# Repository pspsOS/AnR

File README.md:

# AnR: PSPS Avionics and Recovery GitHub
This document was last edited by Jeffrey Kaji on *4 Feb 2021*. <br/>
View our license [here](LICENSE)

## MITCH_2021
**Multi-Instrument Telemetry Computer Hardware** for PSPS 2021 Rocket<br> 
Important Macros: <br>
``getBit(A, X)`` : gets the *"Xth"* bit of *"A"*.<br>
``setBit(A, X, V)`` : sets the *"Xth"* bit of *"A"* to *"V"*.<br><br>

#### Quick Links
* [Documentation Folder **Docs/**](../Docs/README.md)
* [**Recovery-Avionics Jira**](https://psps-recovery-avionics.atlassian.net/jira/software/projects/AV/boards/2)
* [**SRAD Software Confluence Page**](https://psps-recovery-avionics.atlassian.net/wiki/spaces/PSPS/pages/31457281/SRAD+Software)
* [**Task Flowcharts Google Drive Folder**](https://drive.google.com/drive/u/0/folders/1KGmiUlNgTaysgdSle6QIzn_O4cT77nek)
* [**Hardware Datasheets Google Drive Folder**](https://drive.google.com/drive/u/0/folders/14jC0XhoOVIF4Ko5ylgHbCWUhaxgak8n0)

---
**Creating a *README.md*?** <br />
 Try using this free online editor that makes it super easy: 
<https://jbt.github.io/markdown-editor/>

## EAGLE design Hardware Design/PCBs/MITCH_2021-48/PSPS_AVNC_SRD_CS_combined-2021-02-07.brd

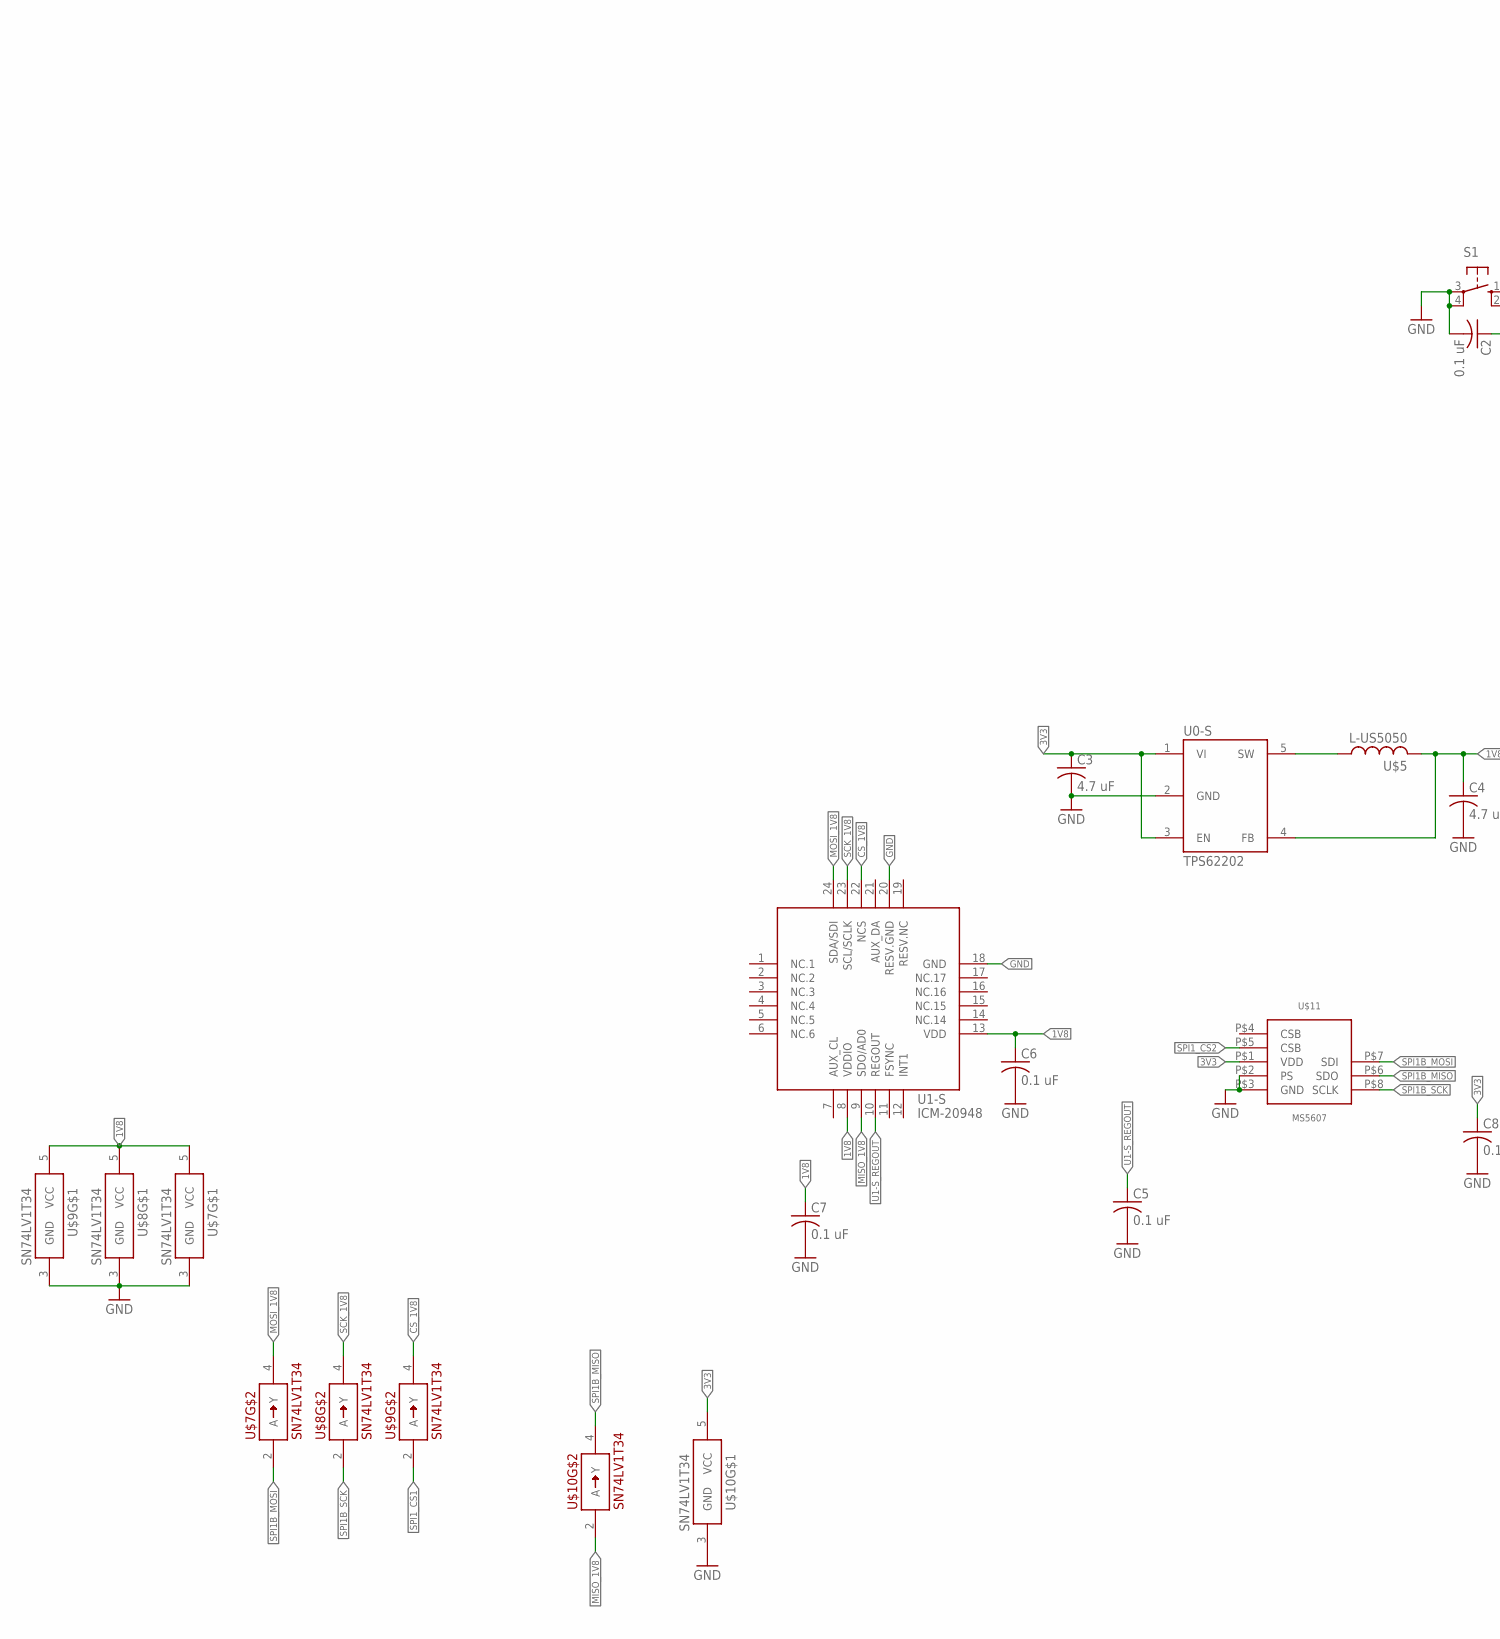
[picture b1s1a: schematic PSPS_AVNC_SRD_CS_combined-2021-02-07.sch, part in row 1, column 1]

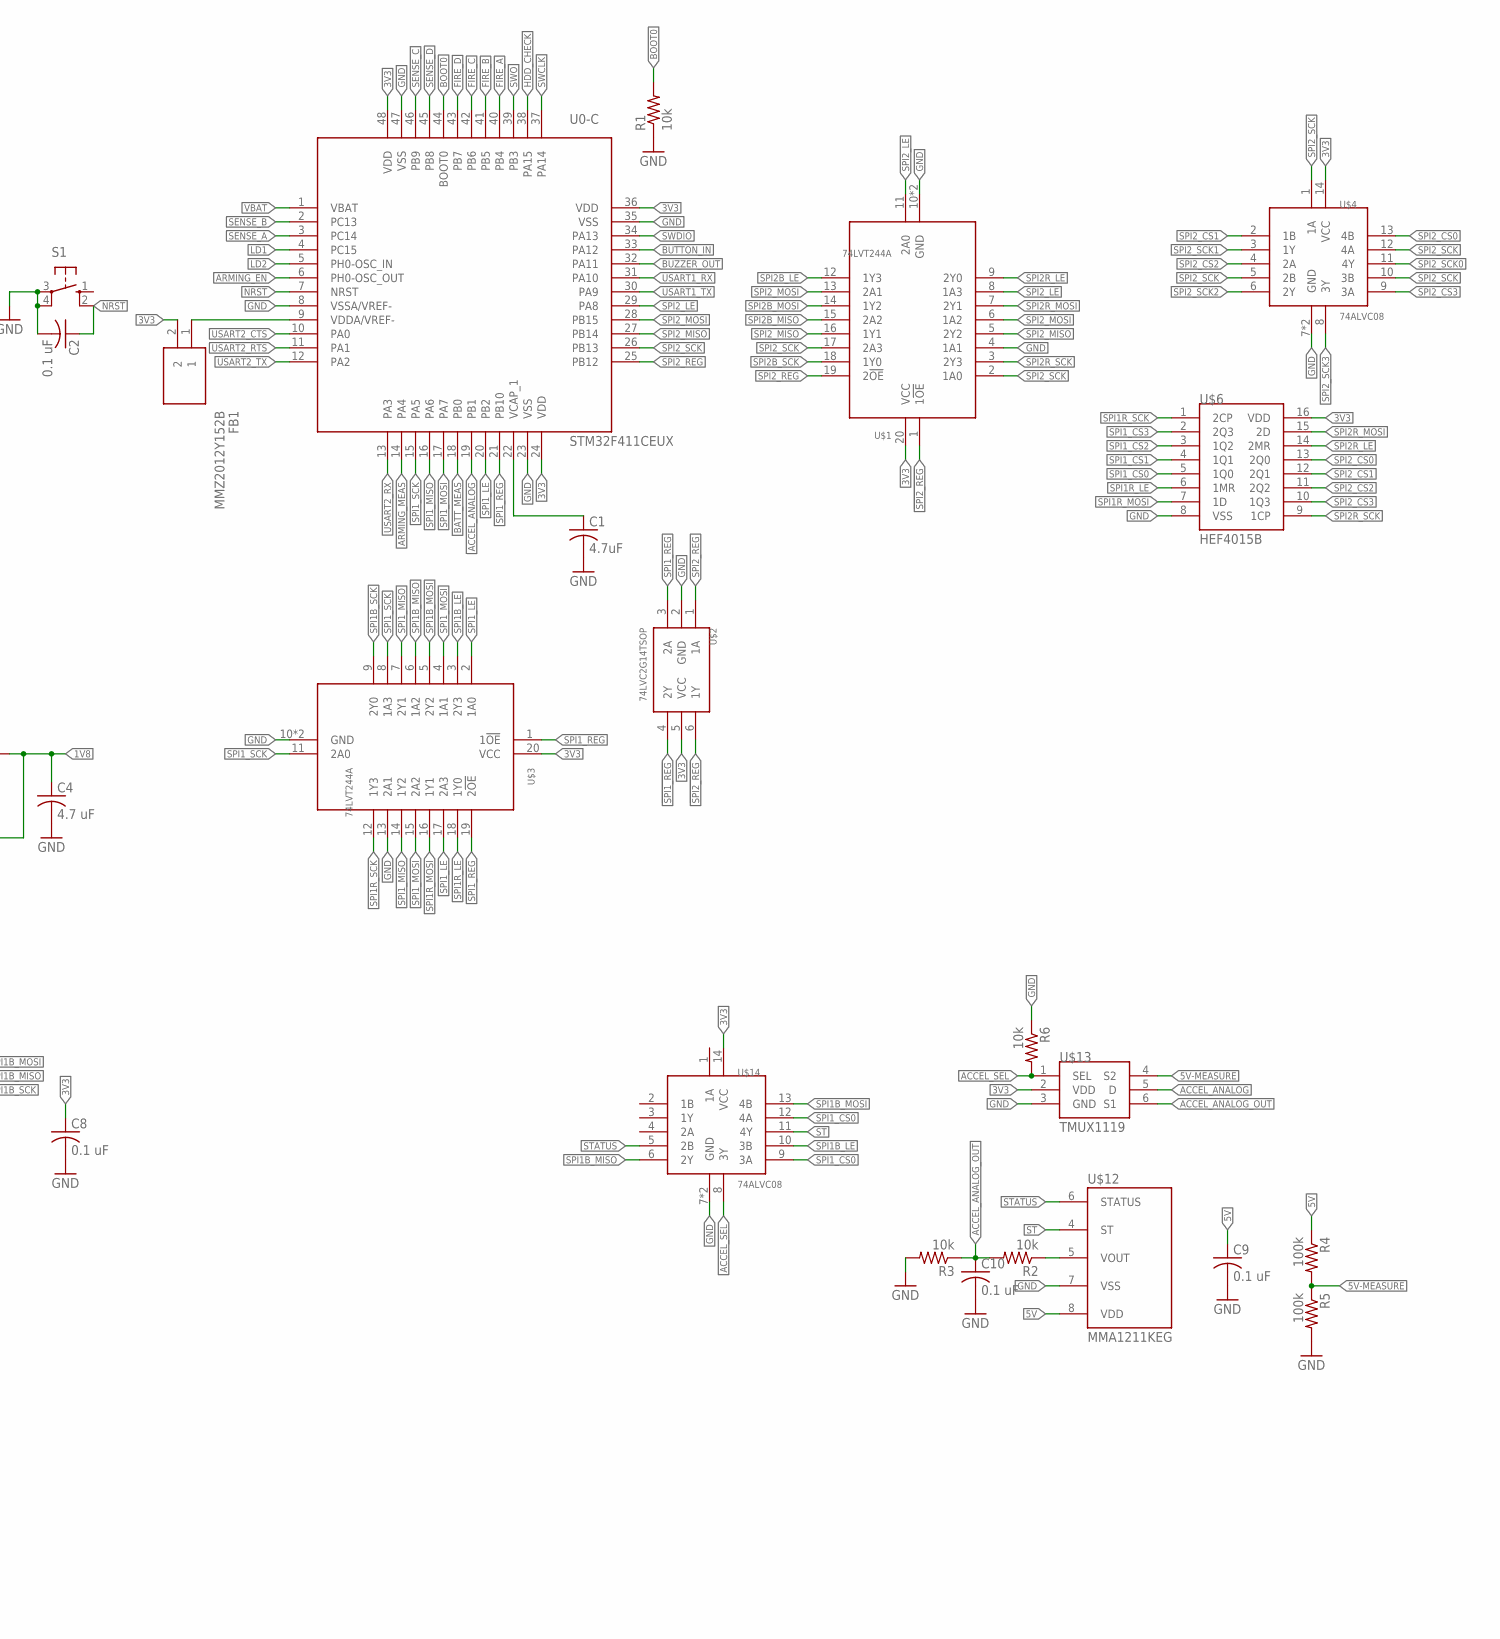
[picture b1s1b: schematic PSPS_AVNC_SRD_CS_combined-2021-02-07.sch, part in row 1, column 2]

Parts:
C1: 4.7uF; C0805
C2, C5, C6, C7, C8, C9, C10: 0.1 uF; C0805
C3, C4: 4.7 uF; C0805
FB1: MMZ2012Y152B; BEADC2012X105N
R1, R2, R3, R6: 10k; M0805
R4, R5: 100k; M0805
S1: 10-XX; B3F-10XX
U0-C: STM32F411CEUX; QFN50P700X700X50-49T560N
U0-S: TPS62202; SOT95P280X145-5
U1-S: ICM-20948; QFN40P300X300X105-25T159X175
U$1, U$3: 74LVT244A; QFN50P450X250X100-21T300X100N
U$2: 74LVC2G14TSOP; SOP95P280X110-6N
U$4, U$14: 74ALVC08; QFN50P300X250X100-15T150X100N
U$5: L-US5050; INDDFN1250X1250X600-2N
U$6: HEF4015B; SOIC127P600X265-16N
U$7, U$8, U$9, U$10: SN74LV1T34; SOT65P210X110-5
U$11: MS5607
U$12: MMA1211KEG; SOIC127P1041X355-16N
U$13: TMUX1119; SOP95P280X145-6N

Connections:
1V8: C4.1, C6.1, C7.1, U0-S.4 (FB), U1-S.8 (VDDIO), U1-S.13 (VDD), U$5.2, U$7.5 (VCC), U$8.5 (VCC), U$9.5 (VCC)
3V3: C3.1, C8.1, FB1.2, U0-C.24 (VDD), U0-C.36 (VDD), U0-C.48 (VDD), U0-S.1 (VI), U0-S.3 (EN), U$1.20 (VCC), U$2.5 (VCC), U$3.20 (VCC), U$4.14 (VCC), U$6.16 (VDD), U$10.5 (VCC), U$11.P$1 (VDD), U$13.2 (VDD), U$14.14 (VCC)
5V: C9.1, R4.1, U$12.8 (VDD)
5V-MEASURE: R4.2, R5.1, U$13.4 (S2)
!SPI1_REG!: U$2.4 (2Y), U$3.19 (2!OE!)
!SPI2_REG!: U$1.1 (1!OE!), U$2.6 (1Y)
ACCEL_ANALOG: U0-C.19 (PB1), U$13.5 (D)
ACCEL_ANALOG_OUT: C10.1, R2.2, R3.1, U$13.6 (S1)
ACCEL_SEL: R6.2, U$13.1 (SEL), U$14.8 (3Y)
ARMING_EN: U0-C.6 (PH0-OSC_OUT)
ARMING_MEAS: U0-C.14 (PA4)
BATT_MEAS: U0-C.18 (PB0)
BOOT0: R1.2, U0-C.44 (BOOT0)
BUTTON_IN: U0-C.33 (PA12)
BUZZER_OUT: U0-C.32 (PA11)
CS_1V8: U1-S.22 (NCS), U$9.4 (Y)
FIRE_A: U0-C.40 (PB4)
FIRE_B: U0-C.41 (PB5)
FIRE_C: U0-C.42 (PB6)
FIRE_D: U0-C.43 (PB7)
GND: C1.2, C2.2, C3.2, C4.2, C5.2, C6.2, C7.2, C8.2, C9.2, C10.2, R1.1, R3.2, R5.2, R6.1, S1.3, S1.4 (P1), U0-C.8 (VSSA/VREF-), U0-C.23 (VSS), U0-C.35 (VSS), U0-C.47 (VSS), U0-S.2 (GND), U1-S.18 (GND), U1-S.20 (RESV.GND), U$1.4 (1A1), U$1.10 (GND), U$1.21 (GND), U$2.2 (GND), U$3.10 (GND), U$3.13 (2A1), U$3.21 (GND), U$4.7 (GND), U$4.15 (GND), U$6.8 (VSS), U$7.3 (GND), U$8.3 (GND), U$9.3 (GND), U$10.3 (GND), U$11.P$2 (PS), U$11.P$3 (GND), U$12.7 (VSS), U$13.3 (GND), U$14.7 (GND), U$14.15 (GND)
HDD_CHECK: U0-C.38 (PA15)
LD1: U0-C.4 (PC15)
LD2: U0-C.5 (PH0-OSC_IN)
MISO_1V8: U1-S.9 (SDO/AD0), U$10.2 (A)
MOSI_1V8: U1-S.24 (SDA/SDI), U$7.4 (Y)
NRST: C2.1, S1.2 (S1), U0-C.7 (NRST)
SCK_1V8: U1-S.23 (SCL/SCLK), U$8.4 (Y)
SENSE_A: U0-C.3 (PC14)
SENSE_B: U0-C.2 (PC13)
SENSE_C: U0-C.46 (PB9)
SENSE_D: U0-C.45 (PB8)
SPI1B_LE: U$3.3 (2Y3), U$14.10 (3B)
SPI1B_MISO: U$3.6 (1A2), U$10.4 (Y), U$11.P$6 (SDO), U$14.6 (2Y)
SPI1B_MOSI: U$3.5 (2Y2), U$7.2 (A), U$11.P$7 (SDI), U$14.13 (4B)
SPI1B_SCK: U$3.9 (2Y0), U$8.2 (A), U$11.P$8 (SCLK)
SPI1R_LE: U$3.18 (1Y0), U$6.6 (1MR)
SPI1R_MOSI: U$3.16 (1Y1), U$6.7 (1D)
SPI1R_SCK: U$3.12 (1Y3), U$6.1 (2CP)
SPI1_CS0: U$6.5 (1Q0), U$14.9 (3A), U$14.12 (4A)
SPI1_CS1: U$6.4 (1Q1), U$9.2 (A)
SPI1_CS2: U$6.3 (1Q2), U$11.P$5 (CSB)
SPI1_CS3: U$6.2 (2Q3)
SPI1_LE: U0-C.20 (PB2), U$3.2 (1A0), U$3.17 (2A3)
SPI1_MISO: U0-C.16 (PA6), U$3.7 (2Y1), U$3.14 (1Y2)
SPI1_MOSI: U0-C.17 (PA7), U$3.4 (1A1), U$3.15 (2A2)
SPI1_REG: U0-C.21 (PB10), U$2.3 (2A), U$3.1 (1!OE!)
SPI1_SCK: U0-C.15 (PA5), U$3.8 (1A3), U$3.11 (2A0)
SPI2B_LE: U$1.12 (1Y3)
SPI2B_MISO: U$1.15 (2A2)
SPI2B_MOSI: U$1.14 (1Y2)
SPI2B_SCK: U$1.18 (1Y0)
SPI2R_LE: U$1.9 (2Y0), U$6.14 (2MR)
SPI2R_MOSI: U$1.7 (2Y1), U$6.15 (2D)
SPI2R_SCK: U$1.3 (2Y3), U$6.9 (1CP)
SPI2_CS0: U$4.13 (4B), U$6.13 (2Q0)
SPI2_CS1: U$4.2 (1B), U$6.12 (2Q1)
SPI2_CS2: U$4.4 (2A), U$6.11 (2Q2)
SPI2_CS3: U$4.9 (3A), U$6.10 (1Q3)
SPI2_LE: U0-C.29 (PA8), U$1.8 (1A3), U$1.11 (2A0)
SPI2_MISO: U0-C.27 (PB14), U$1.5 (2Y2), U$1.16 (1Y1)
SPI2_MOSI: U0-C.28 (PB15), U$1.6 (1A2), U$1.13 (2A1)
SPI2_REG: U0-C.25 (PB12), U$1.19 (2!OE!), U$2.1 (1A)
SPI2_SCK: U0-C.26 (PB13), U$1.2 (1A0), U$1.17 (2A3), U$4.1 (1A), U$4.5 (2B), U$4.10 (3B), U$4.12 (4A)
SPI2_SCK0: U$4.11 (4Y)
SPI2_SCK1: U$4.3 (1Y)
SPI2_SCK2: U$4.6 (2Y)
SPI2_SCK3: U$4.8 (3Y)
ST: U$12.4 (ST), U$14.11 (4Y)
STATUS: U$12.6 (STATUS), U$14.5 (2B)
SWCLK: U0-C.37 (PA14)
SWDIO: U0-C.34 (PA13)
SWO: U0-C.39 (PB3)
U0-S_SW: U0-S.5 (SW), U$5.1
U0-S_VOUT: R2.1, U$12.5 (VOUT)
U1-S_REGOUT: C5.1, U1-S.10 (REGOUT)
USART1_RX: U0-C.31 (PA10)
USART1_TX: U0-C.30 (PA9)
USART2_CTS: U0-C.10 (PA0)
USART2_RTS: U0-C.11 (PA1)
USART2_RX: U0-C.13 (PA3)
USART2_TX: U0-C.12 (PA2)
VBAT: U0-C.1 (VBAT)
VCAP_1: C1.1, U0-C.22 (VCAP_1)
VDDA: FB1.1, U0-C.9 (VDDA/VREF-)

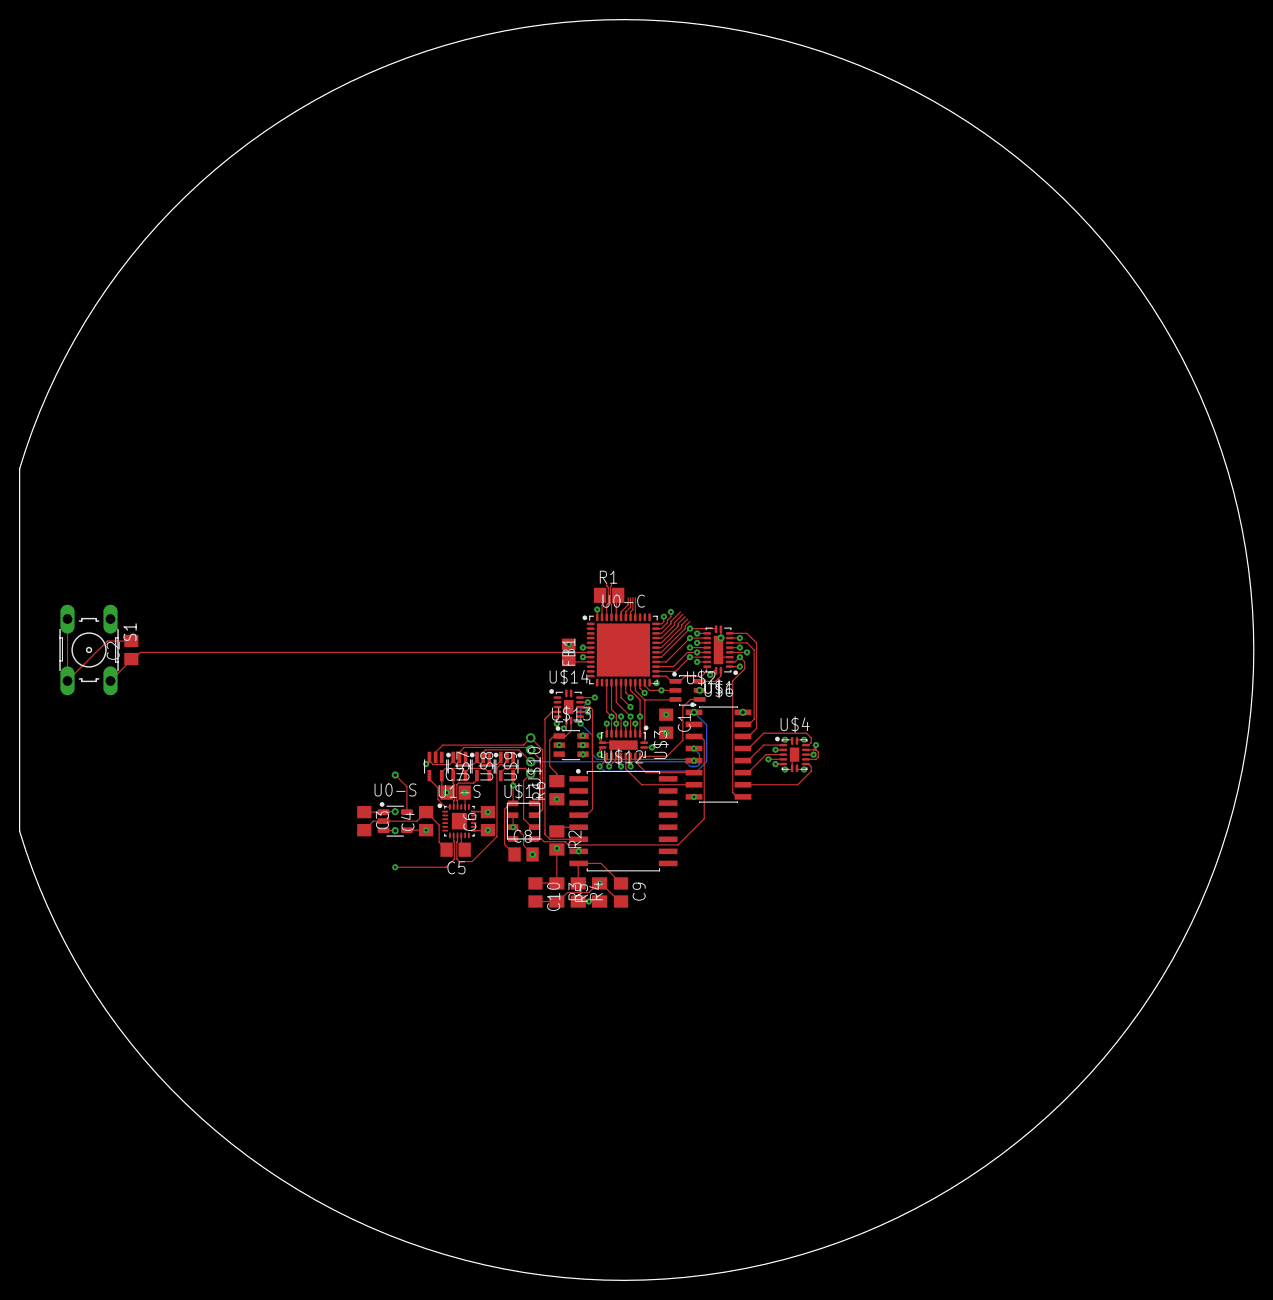
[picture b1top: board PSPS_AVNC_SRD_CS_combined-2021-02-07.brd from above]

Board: 4 copper layers, 129.8 x 132.6 mm, 35 parts (1 on the bottom side), 50 nets.

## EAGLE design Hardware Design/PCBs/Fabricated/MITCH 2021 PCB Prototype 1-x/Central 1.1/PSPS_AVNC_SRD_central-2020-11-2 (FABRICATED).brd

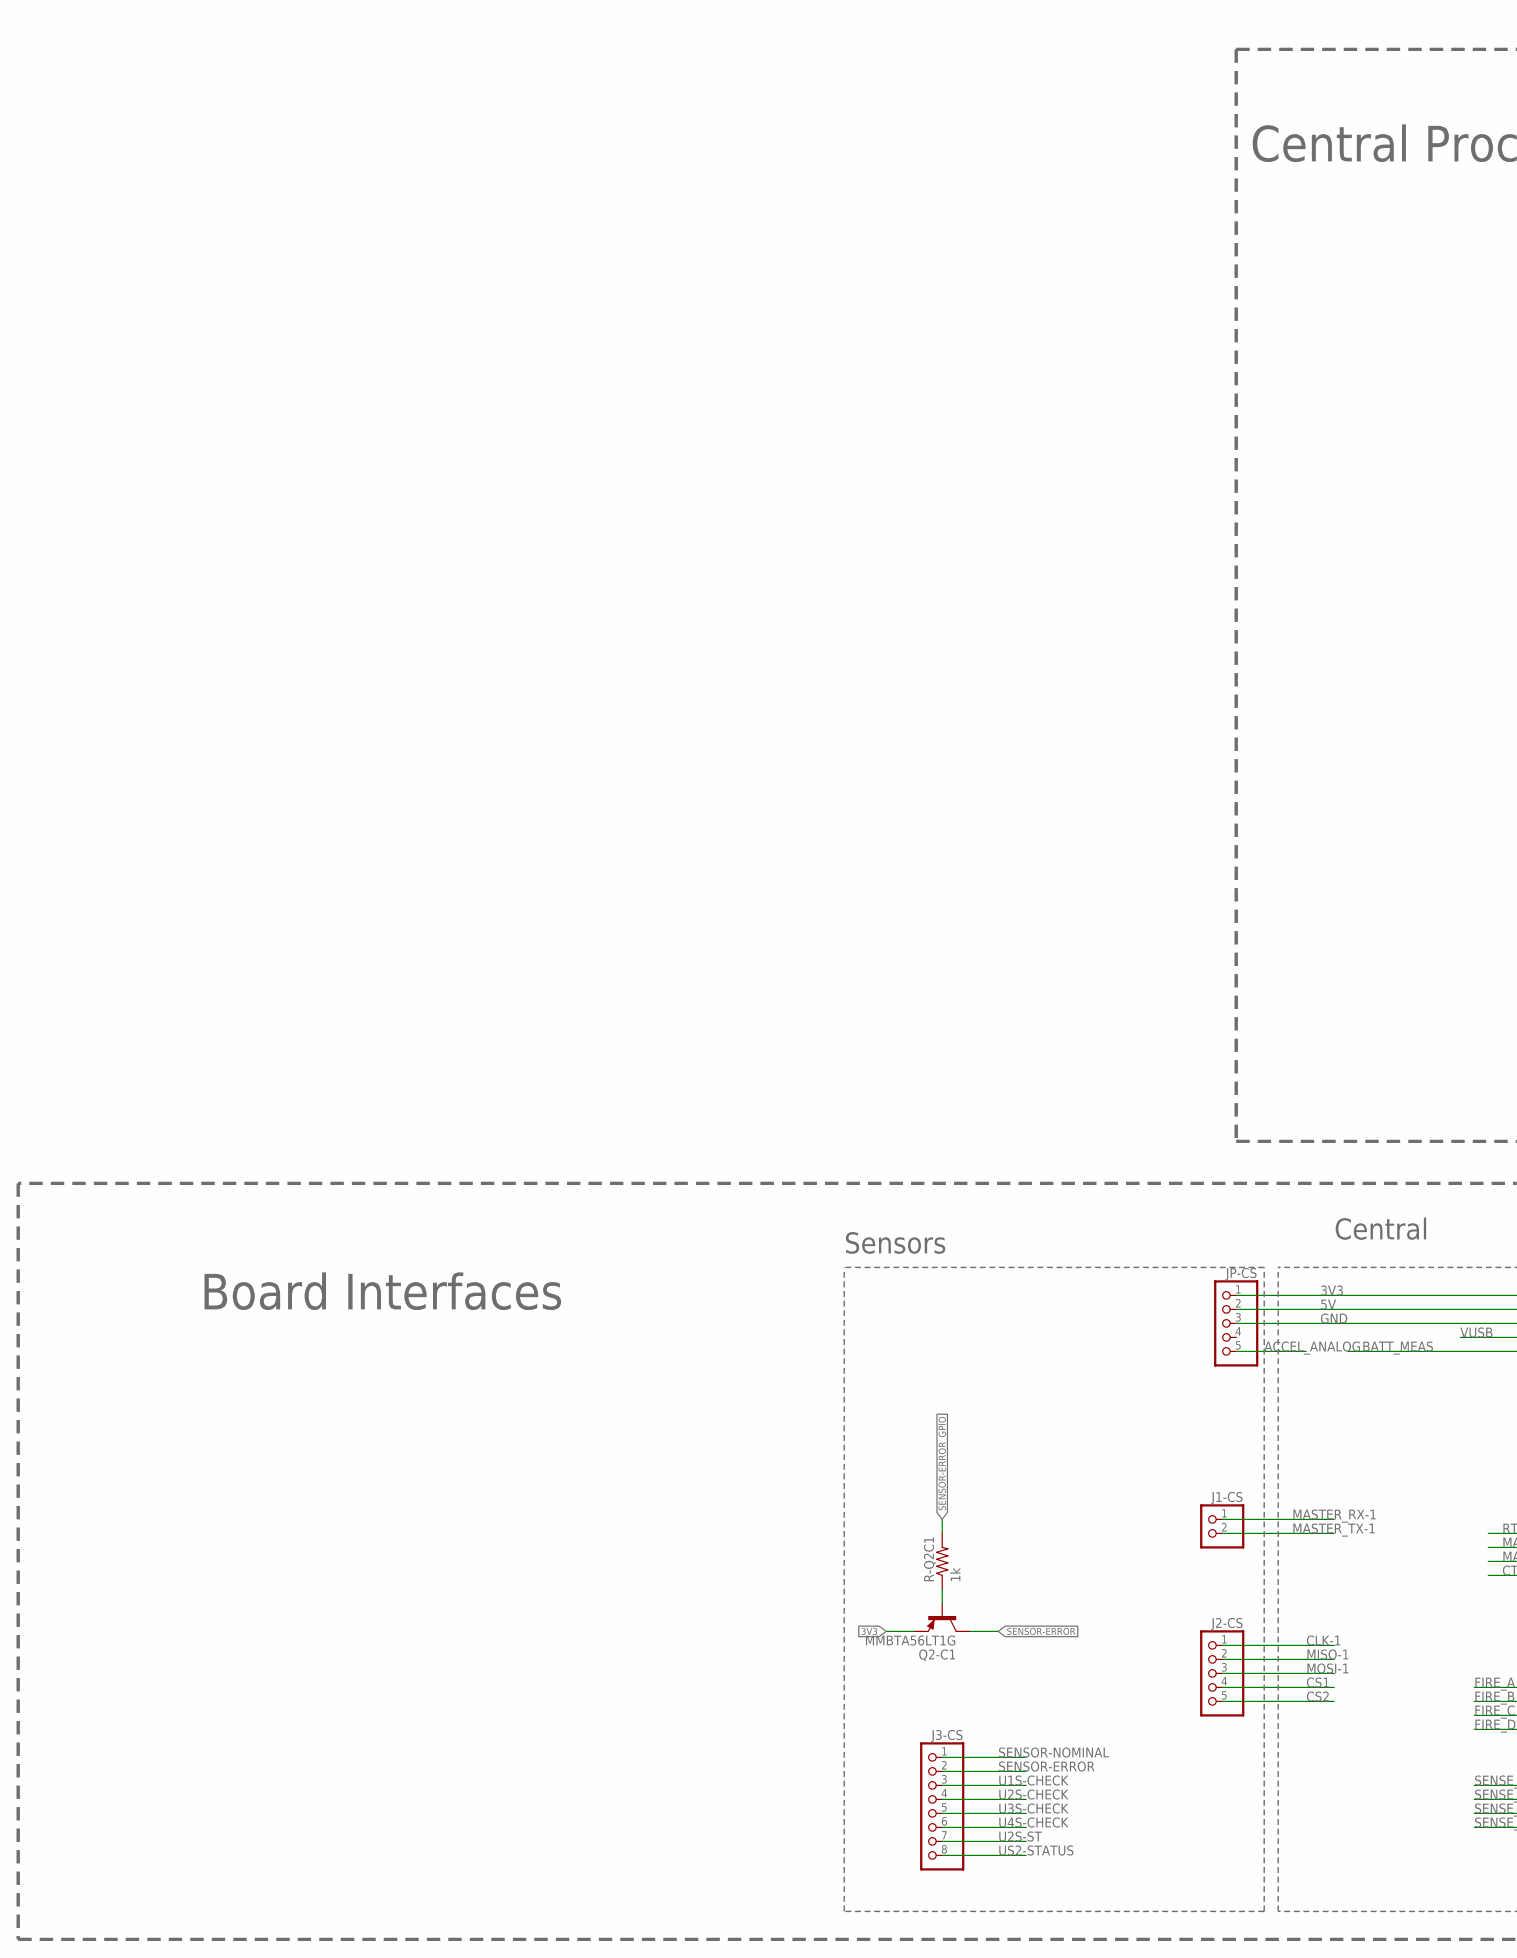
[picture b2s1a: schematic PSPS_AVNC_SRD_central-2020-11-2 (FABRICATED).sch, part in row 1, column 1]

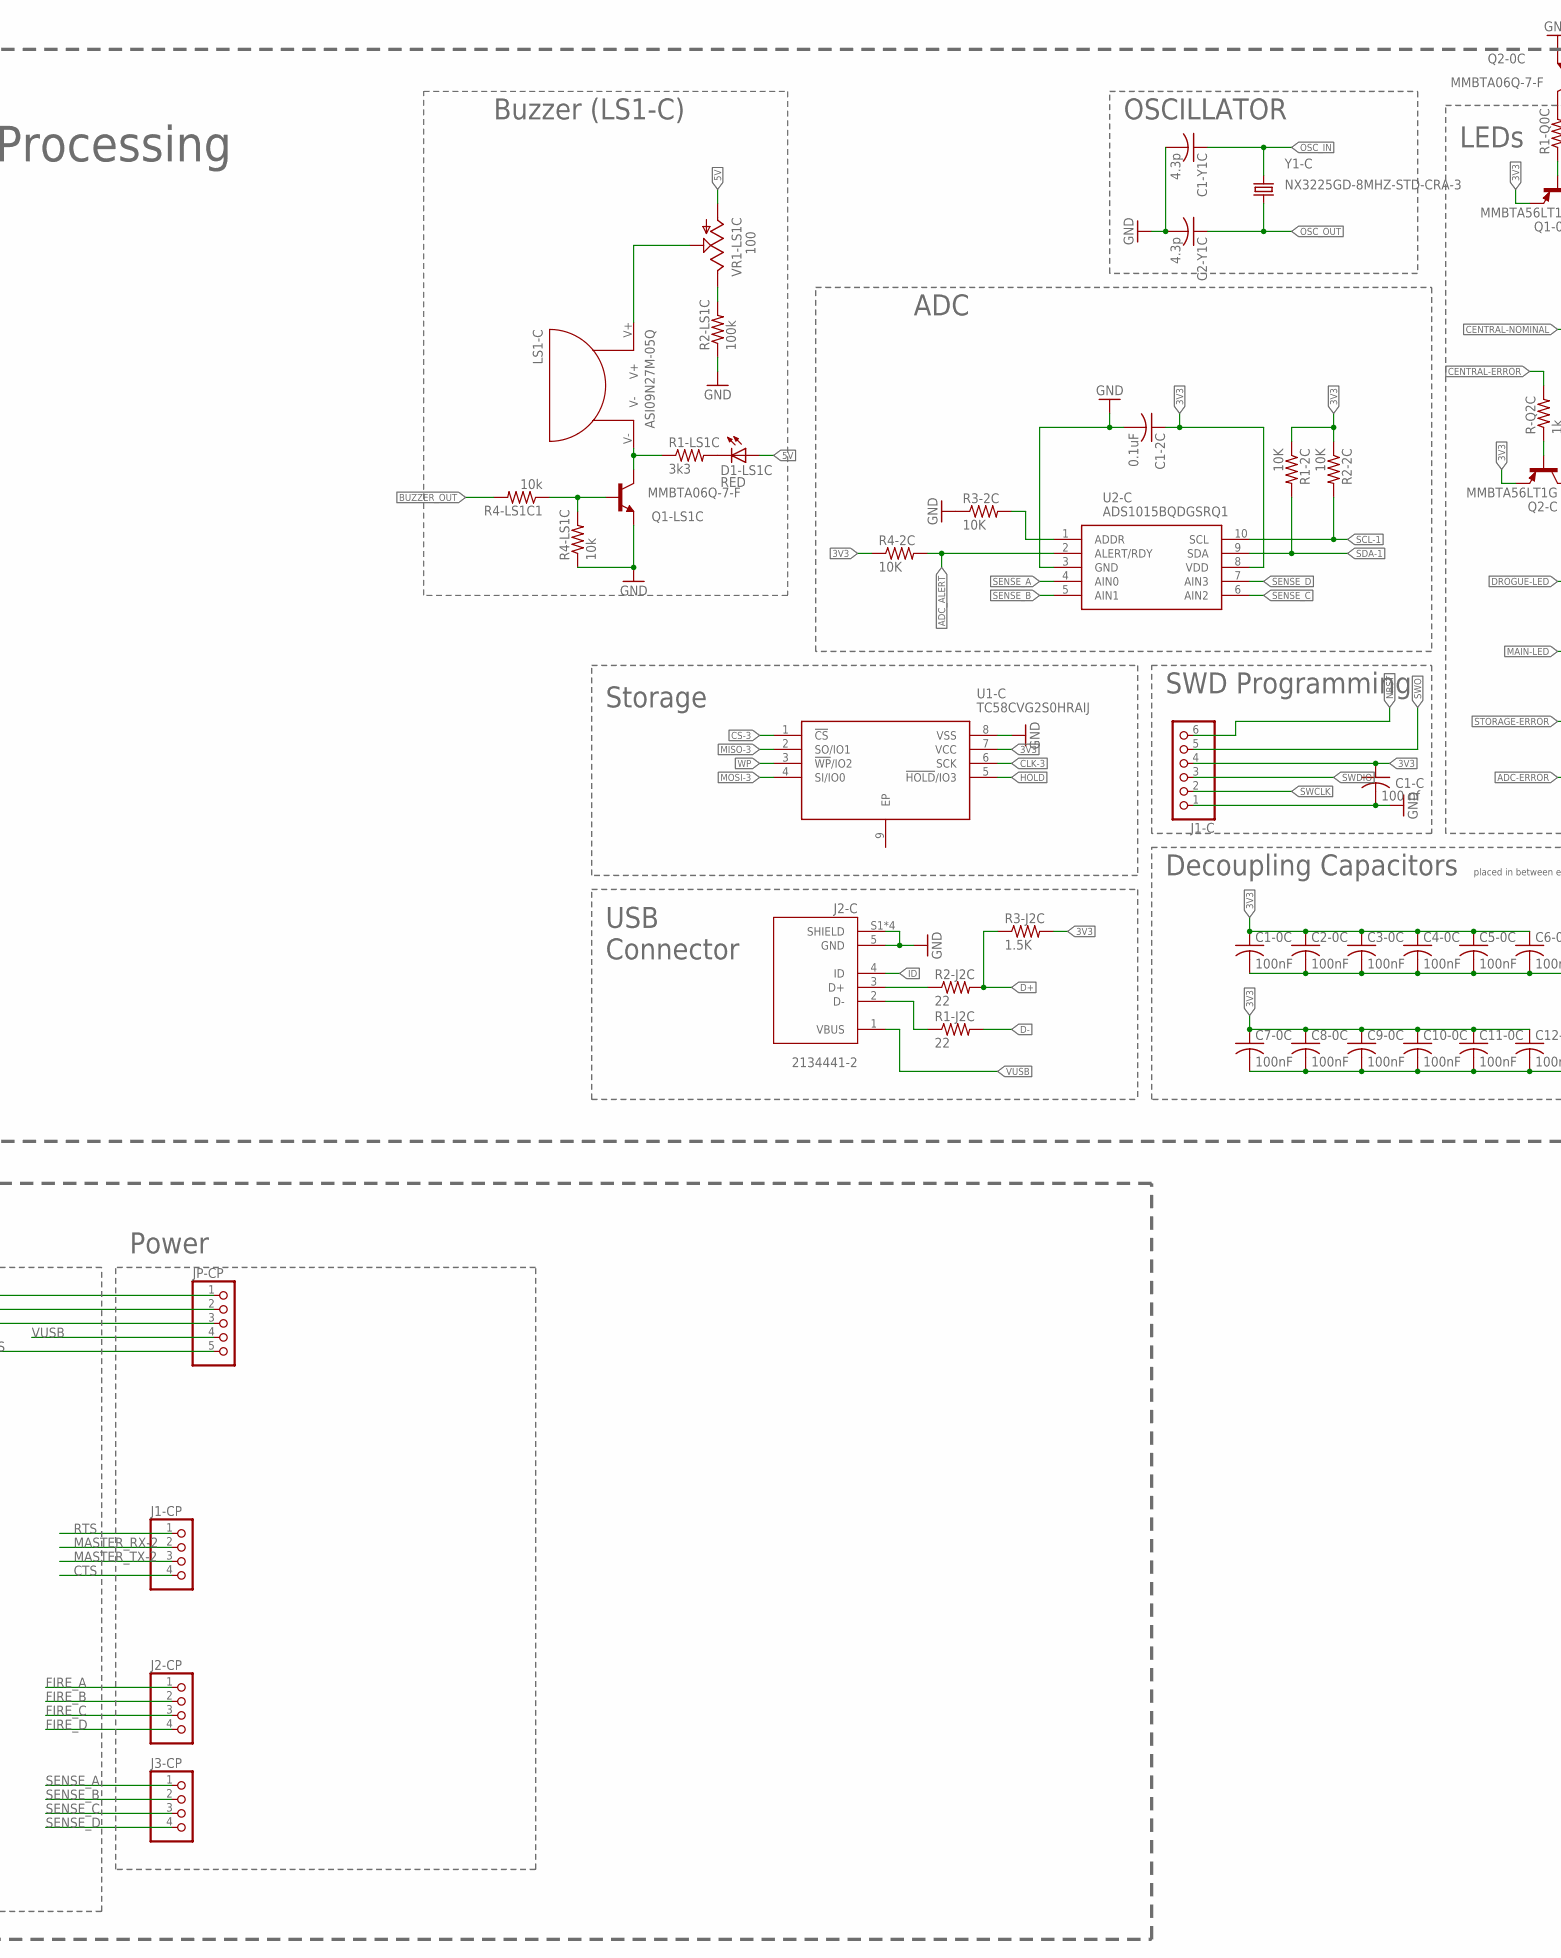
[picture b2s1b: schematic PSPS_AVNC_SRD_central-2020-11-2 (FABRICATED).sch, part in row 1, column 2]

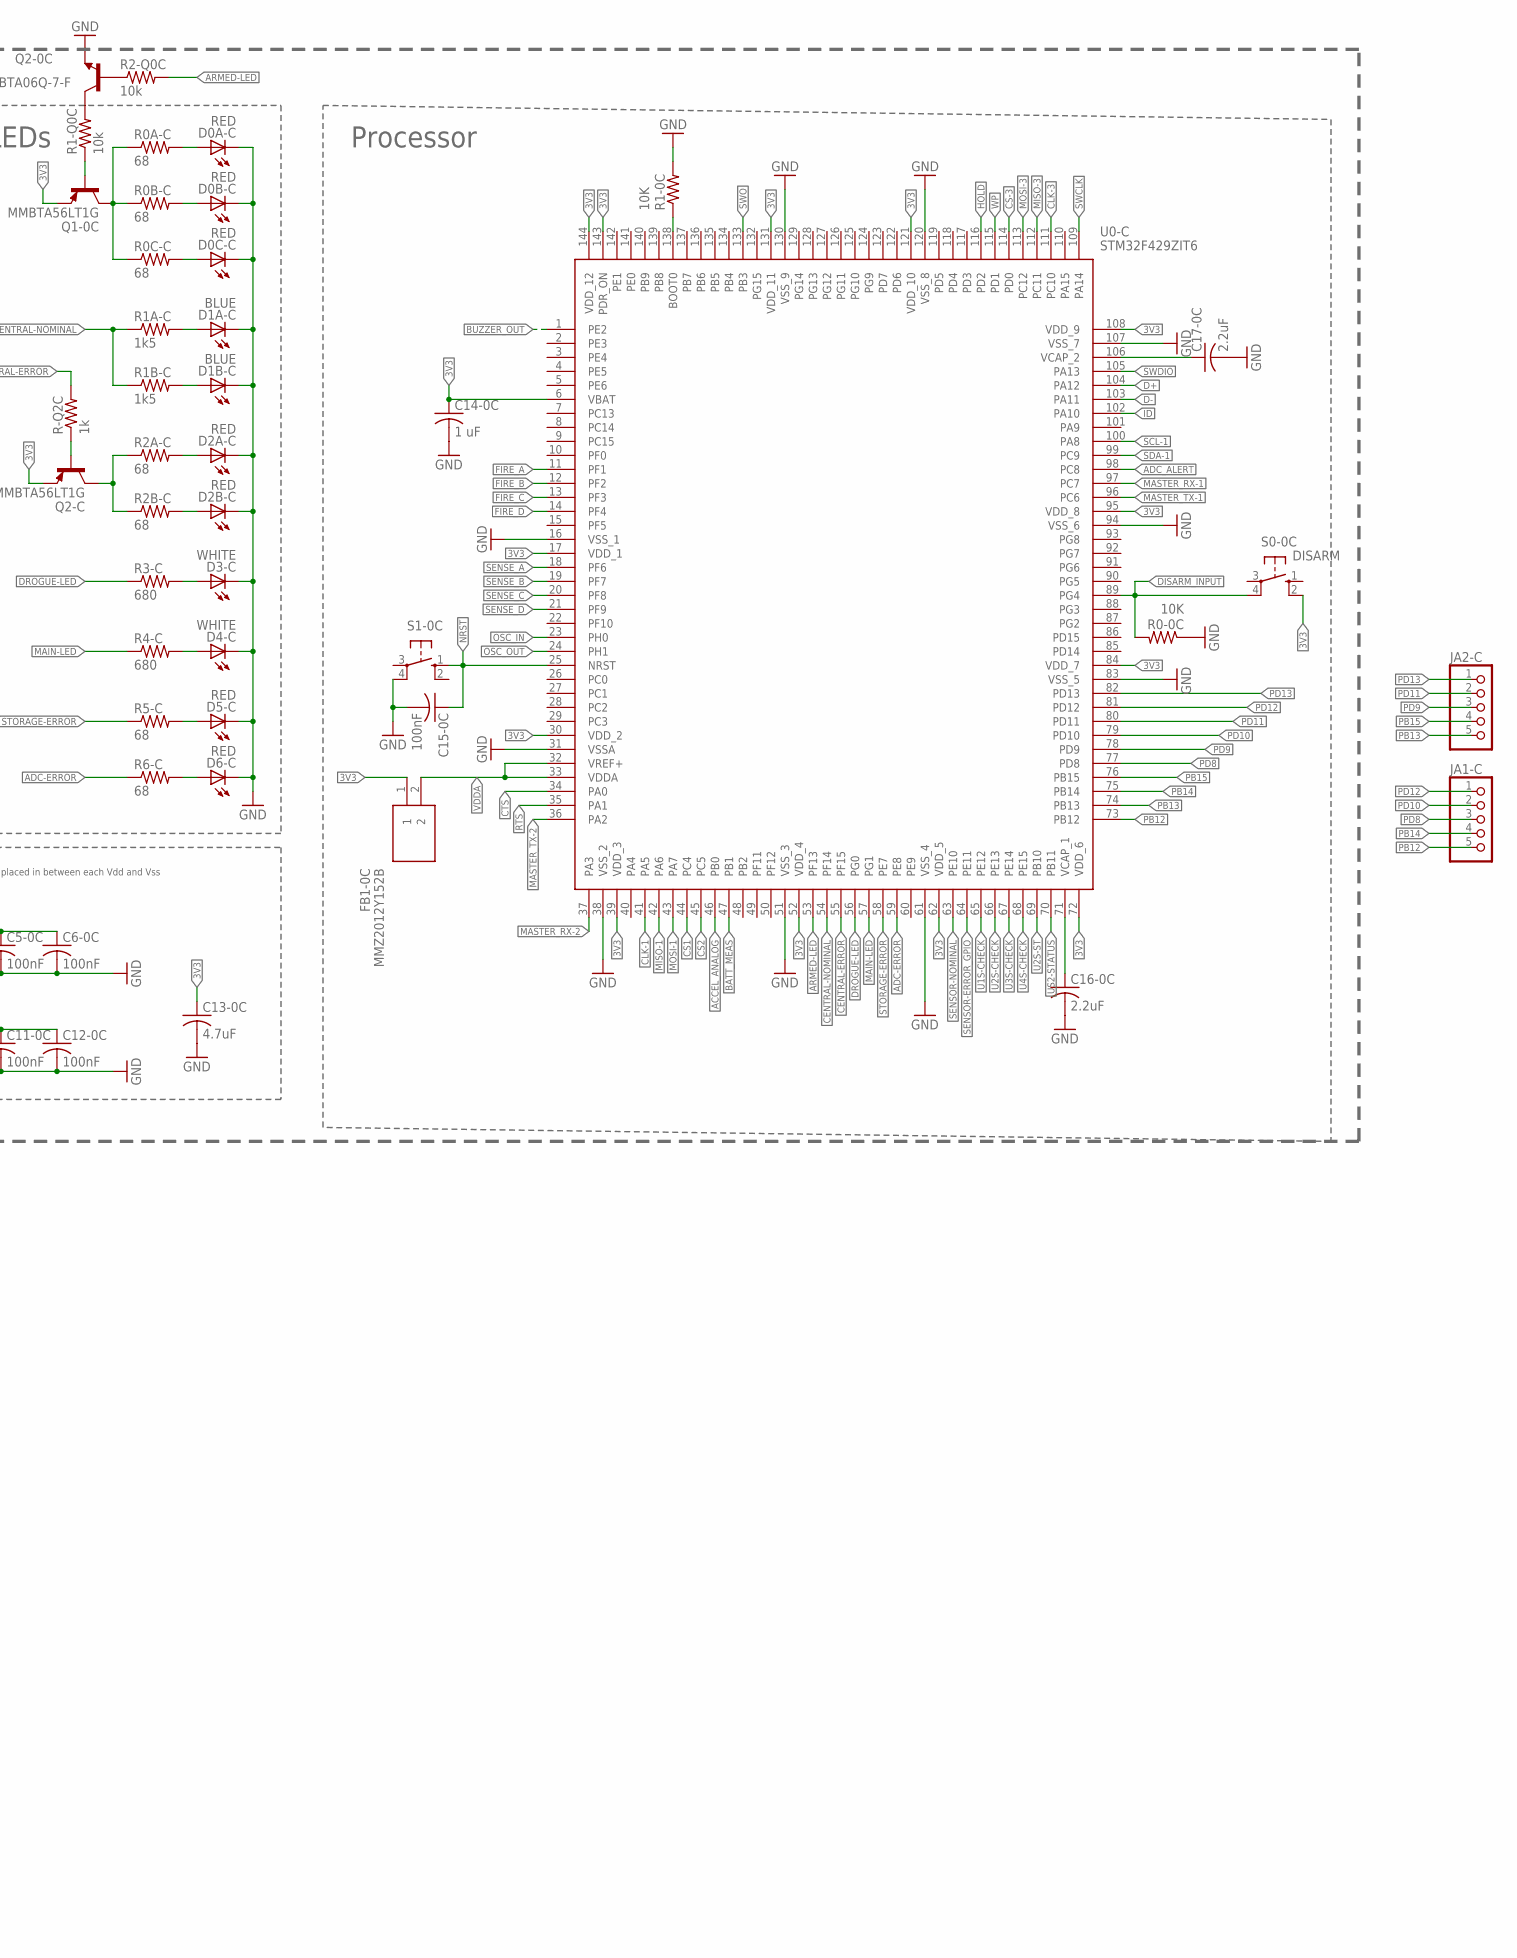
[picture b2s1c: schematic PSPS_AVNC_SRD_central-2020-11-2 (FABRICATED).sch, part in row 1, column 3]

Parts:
C1-0C, C2-0C, C3-0C, C4-0C, C5-0C, C6-0C, C7-0C, C8-0C, C9-0C, C10-0C, C11-0C, C12-0C, C15-0C: 100nF; C0805
C1-2C: 0.1uF; C0805
C1-C: 100 nf; C0805
C1-Y1C, C2-Y1C: 4.3p; C0805
C13-0C: 4.7uF; C0805
C14-0C: 1 uF; C0805
C16-0C, C17-0C: 2.2uF; C0805
D0A-C, D0B-C, D0C-C, D1-LS1C, D2A-C, D2B-C, D5-C, D6-C: RED; CHIPLED_0805
D1A-C, D1B-C: BLUE; CHIPLED_0805
D3-C, D4-C: WHITE; CHIPLED_0805
FB1-0C: MMZ2012Y152B; BEADC2012X105N
J1-C: PINHD-1X6; 1X06
J1-CP, J2-CP, J3-CP: PINHD-1X4; 1X04
J1-CS: PINHD-1X2; 1X02
J2-C: 2134441-2; TE_2134441-2
J2-CS: PINHD-1X5; 1X05
J3-CS: PINHD-1X8; 1X08
JA1-C, JA2-C: PINHD-1X5; 1X05
JP-CP: PINHD-1X5; 1X05
JP-CS: PINHD-1X5; 1X05
LS1-C: ASI09N27M-05Q
Q1-0C, Q2-C, Q2-C1: MMBTA56LT1G; SOT23
Q1-LS1C, Q2-0C: MMBTA06Q-7-F; SOT23
R0-0C, R1-0C, R1-2C, R2-2C, R3-2C, R4-2C: 10K; R0805
R0A-C, R0B-C, R0C-C, R2A-C, R2B-C, R5-C, R6-C: 68; M0805
R1-J2C, R2-J2C: 22; M0805
R1-LS1C: 3k3; R0805
R1-Q0C, R2-Q0C: 10k; M0805
R1A-C, R1B-C: 1k5; M0805
R2-LS1C: 100k; R0805
R3-C, R4-C: 680; M0805
R3-J2C: 1.5K; M0805
R4-LS1C, R4-LS1C1: 10k; R0805
R-Q2C, R-Q2C1: 1k; M0805
S0-0C: DISARM; B3F-10XX
S1-0C: 10-XX; B3F-10XX
U0-C: STM32F429ZIT6; QFP50P2200X2200X160-144N
U1-C: TC58CVG2S0HRAIJ; SON127P800X600X80-9N
U2-C: ADS1015BQDGSRQ1; SOP50P490X110-10N
VR1-LS1C: 100; LI10
Y1-C: NX3225GD-8MHZ-STD-CRA-3; NX3225GD

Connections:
3V3: C1-0C.1, C1-2C.1, C1-C.1, C2-0C.1, C3-0C.1, C4-0C.1, C5-0C.1, C6-0C.1, C7-0C.1, C8-0C.1, C9-0C.1, C10-0C.1, C11-0C.1, C12-0C.1, C13-0C.1, C14-0C.1, FB1-0C.1, J1-C.4, JP-CP.1, JP-CS.1, Q1-0C.2 (E), Q2-C.2 (E), Q2-C1.2 (E), R1-2C.1, R2-2C.1, R3-J2C.2, R4-2C.1, S0-0C.2 (S1), U0-C.6 (VBAT), U0-C.17 (VDD_1), U0-C.30 (VDD_2), U0-C.39 (VDD_3), U0-C.52 (VDD_4), U0-C.62 (VDD_5), U0-C.72 (VDD_6), U0-C.84 (VDD_7), U0-C.95 (VDD_8), U0-C.108 (VDD_9), U0-C.121 (VDD_10), U0-C.131 (VDD_11), U0-C.143 (PDR_ON), U0-C.144 (VDD_12), U1-C.7 (VCC), U2-C.8 (VDD)
5V: D1-LS1C.A, JP-CP.2, JP-CS.2, VR1-LS1C.A
ACCEL_ANALOG: JP-CS.5, U0-C.46 (PB0)
ADC-ERROR: R6-C.1, U0-C.59 (PE8)
ADC_ALERT: R4-2C.2, U0-C.98 (PC8), U2-C.2 (ALERT/RDY)
ADDR: R3-2C.2, U2-C.1 (ADDR)
ARMED-LED: R2-Q0C.2, U0-C.53 (PF13)
BATT_MEAS: JP-CP.5, U0-C.47 (PB1)
BOOT0: R1-0C.1, U0-C.138 (BOOT0)
BUZZER_OUT: R4-LS1C1.2, U0-C.1 (PE2)
CENTRAL-ERROR: R-Q2C.2, U0-C.55 (PF15)
CENTRAL-NOMINAL: R1A-C.1, R1B-C.1, U0-C.54 (PF14)
CLK-1: J2-CS.1, U0-C.41 (PA5)
CLK-3: U0-C.111 (PC10), U1-C.6 (SCK)
CS1: J2-CS.4, U0-C.44 (PC4)
CS2: J2-CS.5, U0-C.45 (PC5)
CS-3: U0-C.114 (PD0), U1-C.1 (!CS)
CTS: J1-CP.4, U0-C.34 (PA0)
D1-LS1C_R1-LS1C: D1-LS1C.C, R1-LS1C.2
D+: R2-J2C.2, R3-J2C.1, U0-C.104 (PA12)
D+_R2-J1C: J2-C.3 (D+), R2-J2C.1
D-: R1-J2C.2, U0-C.103 (PA11)
D-_R1-J1C: J2-C.2 (D-), R1-J2C.1
DISARM_INPUT: R0-0C.2, S0-0C.4 (P1), U0-C.89 (PG4)
DROGUE-LED: R3-C.1, U0-C.56 (PG0)
FIRE_A: J2-CP.1, U0-C.11 (PF1)
FIRE_B: J2-CP.2, U0-C.12 (PF2)
FIRE_C: J2-CP.3, U0-C.13 (PF3)
FIRE_D: J2-CP.4, U0-C.14 (PF4)
GND: C1-0C.2, C1-2C.2, C1-C.2, C1-Y1C.2, C2-0C.2, C2-Y1C.2, C3-0C.2, C4-0C.2, C5-0C.2, C6-0C.2, C7-0C.2, C8-0C.2, C9-0C.2, C10-0C.2, C11-0C.2, C12-0C.2, C13-0C.2, C14-0C.2, C15-0C.2, C16-0C.2, C17-0C.2, D0A-C.C, D0B-C.C, D0C-C.C, D1A-C.C, D1B-C.C, D2A-C.C, D2B-C.C, D3-C.C, D4-C.C, D5-C.C, D6-C.C, J1-C.1, J2-C.5 (GND), J2-C.S1 (SHIELD), J2-C.S2 (SHIELD), J2-C.S3 (SHIELD), J2-C.S4 (SHIELD), JP-CP.3, JP-CS.3, Q1-LS1C.3 (E), Q2-0C.3 (E), R0-0C.1, R1-0C.2, R2-LS1C.1, R3-2C.1, R4-LS1C.1, S1-0C.4 (P1), U0-C.16 (VSS_1), U0-C.31 (VSSA), U0-C.38 (VSS_2), U0-C.51 (VSS_3), U0-C.61 (VSS_4), U0-C.83 (VSS_5), U0-C.94 (VSS_6), U0-C.107 (VSS_7), U0-C.120 (VSS_8), U0-C.130 (VSS_9), U1-C.8 (VSS), U2-C.3 (GND)
HOLD: U0-C.116 (PD2), U1-C.5 (!HOLD!/IO3)
ID: J2-C.4 (ID), U0-C.102 (PA10)
LS1-C_Q1-LS1C: LS1-C.V-, Q1-LS1C.2 (C), R1-LS1C.1
MAIN-LED: R4-C.1, U0-C.57 (PG1)
MASTER_RX-1: J1-CS.1, U0-C.97 (PC7)
MASTER_RX-2: J1-CP.2, U0-C.37 (PA3)
MASTER_TX-1: J1-CS.2, U0-C.96 (PC6)
MASTER_TX-2: J1-CP.3, U0-C.36 (PA2)
MISO-1: J2-CS.2, U0-C.42 (PA6)
MISO-3: U0-C.112 (PC11), U1-C.2 (SO/IO1)
MOSI-1: J2-CS.3, U0-C.43 (PA7)
MOSI-3: U0-C.113 (PC12), U1-C.4 (SI/IO0)
unnamed: Q2-C1.1 (B), R-Q2C1.1
NRST: C15-0C.1, J1-C.6, S1-0C.1 (S), U0-C.25 (NRST)
OSC_IN: C1-Y1C.1, U0-C.23 (PH0), Y1-C.P$2 (2)
OSC_OUT: C2-Y1C.1, U0-C.24 (PH1), Y1-C.P$1 (1)
PB12: JA1-C.5, U0-C.73 (PB12)
PB13: JA2-C.5, U0-C.74 (PB13)
PB14: JA1-C.4, U0-C.75 (PB14)
PB15: JA2-C.4, U0-C.76 (PB15)
PD8: JA1-C.3, U0-C.77 (PD8)
PD9: JA2-C.3, U0-C.78 (PD9)
PD10: JA1-C.2, U0-C.79 (PD10)
PD11: JA2-C.2, U0-C.80 (PD11)
PD12: JA1-C.1, U0-C.81 (PD12)
PD13: JA2-C.1, U0-C.82 (PD13)
Q0-C_R0-C: Q1-0C.3 (C), R0A-C.1, R0B-C.1, R0C-C.1
Q1-0C_R-1Q0C: Q1-0C.1 (B), R1-Q0C.1
Q2-C_R2-C: Q2-C.3 (C), R2A-C.1, R2B-C.1
R0A-C_D0A-C: D0A-C.A, R0A-C.2
R0B-C_D0B-C: D0B-C.A, R0B-C.2
R0C-C_D0C-C: D0C-C.A, R0C-C.2
R1-Q0C_Q2-0C: Q2-0C.2 (C), R1-Q0C.2
R1A-C_D1A-C: D1A-C.A, R1A-C.2
R1B-C_D1B-C: D1B-C.A, R1B-C.2
R2-LS1C_LS1C: LS1-C.V+, VR1-LS1C.S
R2-Q0C_Q2-0C: Q2-0C.1 (B), R2-Q0C.1
R2A-C_D2A-C: D2A-C.A, R2A-C.2
R2B-C_D2B-C: D2B-C.A, R2B-C.2
R3-C_D3-C: D3-C.A, R3-C.2
R3-LS1C_Q1-LS1C: Q1-LS1C.1 (B), R4-LS1C.2, R4-LS1C1.1
R4-C_D4-C: D4-C.A, R4-C.2
R5-C_D5-C: D5-C.A, R5-C.2
R6-C_D6-C: D6-C.A, R6-C.2
R-Q2C_Q2-C: Q2-C.1 (B), R-Q2C.1
RTS: J1-CP.1, U0-C.35 (PA1)
SCL-1: R2-2C.2, U0-C.100 (PA8), U2-C.10 (SCL)
SDA-1: R1-2C.2, U0-C.99 (PC9), U2-C.9 (SDA)
SENSE_A: J3-CP.1, U0-C.18 (PF6), U2-C.4 (AIN0)
SENSE_B: J3-CP.2, U0-C.19 (PF7), U2-C.5 (AIN1)
SENSE_C: J3-CP.3, U0-C.20 (PF8), U2-C.6 (AIN2)
SENSE_D: J3-CP.4, U0-C.21 (PF9), U2-C.7 (AIN3)
SENSOR-ERROR: J3-CS.2, Q2-C1.3 (C)
SENSOR-ERROR_GPIO: R-Q2C1.2, U0-C.64 (PE11)
SENSOR-NOMINAL: J3-CS.1, U0-C.63 (PE10)
STORAGE-ERROR: R5-C.1, U0-C.58 (PE7)
SWCLK: J1-C.2, U0-C.109 (PA14)
SWDIO: J1-C.3, U0-C.105 (PA13)
SWO: J1-C.5, U0-C.133 (PB3)
U1S-CHECK: J3-CS.3, U0-C.65 (PE12)
U2S-CHECK: J3-CS.4, U0-C.66 (PE13)
U2S-ST: J3-CS.7, U0-C.69 (PB10)
U3S-CHECK: J3-CS.5, U0-C.67 (PE14)
U4S-CHECK: J3-CS.6, U0-C.68 (PE15)
US2-STATUS: J3-CS.8, U0-C.70 (PB11)
VCAP_1: C16-0C.1, U0-C.71 (VCAP_1)
VCAP_2: C17-0C.1, U0-C.106 (VCAP_2)
VDDA: FB1-0C.2, U0-C.32 (VREF+), U0-C.33 (VDDA)
VR1-LS1C_R3-LS1C: R2-LS1C.2, VR1-LS1C.E
VUSB: J2-C.1 (VBUS), JP-CP.4
WP: U0-C.115 (PD1), U1-C.3 (!WP!/IO2)

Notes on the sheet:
Central Processing
placed in between each Vdd and Vss
Processor
Storage
Decoupling Capacitors
SWD Programming
LEDs
ADC
USB Connector
OSCILLATOR
Buzzer (LS1-C)
Central
Power
Sensors
Board Interfaces

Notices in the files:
parts and their libraries:
SparkFun-Connectors: Licensing: Creative Commons ShareAlike 4.0 International - https://creativecommons.org/licenses/by-sa/4.0
crystal-geyer_V1_0: Copyright: Geyer-Electronic
